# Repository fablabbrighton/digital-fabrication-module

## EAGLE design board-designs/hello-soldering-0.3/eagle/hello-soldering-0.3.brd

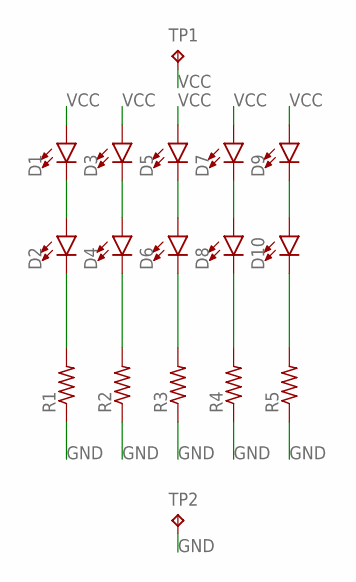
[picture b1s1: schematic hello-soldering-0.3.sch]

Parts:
D1, D2, D3, D4, D5, D6, D7, D8, D9, D10: LED1206; LED-1206
R1, R2, R3, R4, R5: RES-US1206; R1206
TP1, TP2: TPTP20R; TP20R

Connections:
GND: R1.1, R2.1, R3.1, R4.1, R5.1, TP2.TP
unnamed: D1.C, D2.A
unnamed: D2.C, R1.2
unnamed: D3.C, D4.A
unnamed: D4.C, R2.2
unnamed: D5.C, D6.A
unnamed: D6.C, R3.2
unnamed: D8.C, R4.2
unnamed: D10.C, R5.2
unnamed: D7.C, D8.A
unnamed: D9.C, D10.A
VCC: D1.A, D3.A, D5.A, D7.A, D9.A, TP1.TP

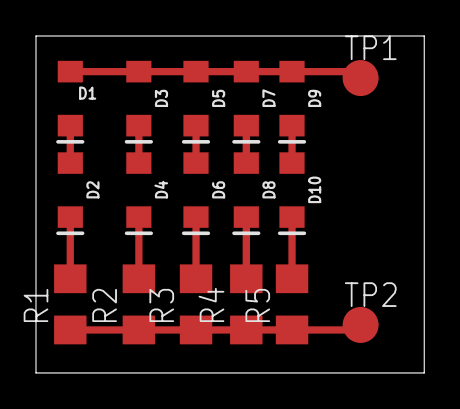
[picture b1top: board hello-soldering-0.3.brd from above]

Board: 2 copper layers, 21.6 x 18.7 mm, 17 parts (0 on the bottom side), 12 nets.

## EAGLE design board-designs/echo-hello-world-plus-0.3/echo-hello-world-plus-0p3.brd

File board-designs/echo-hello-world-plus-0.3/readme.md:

# Readme

This is a minimal ATtiny44-based board, derived from Neil's Echo Hello World board, as used in [Fab Academy Electronics Design week](http://academy.cba.mit.edu/classes/electronics_design/index.html).

It has an additional LED (with current-limiting resistor) and button, to enable simple testing by uploading Arduino blink or button sketches. (Hence the 'Plus' in the name.)

The button needs a pull-up resistor (on the pin, or added externally) to work.

This board is used in our [electronics design week](https://github.com/fablabbrighton/digital-fabrication-module/tree/master/docs/_course-notes/week-5-electronics-design.md).

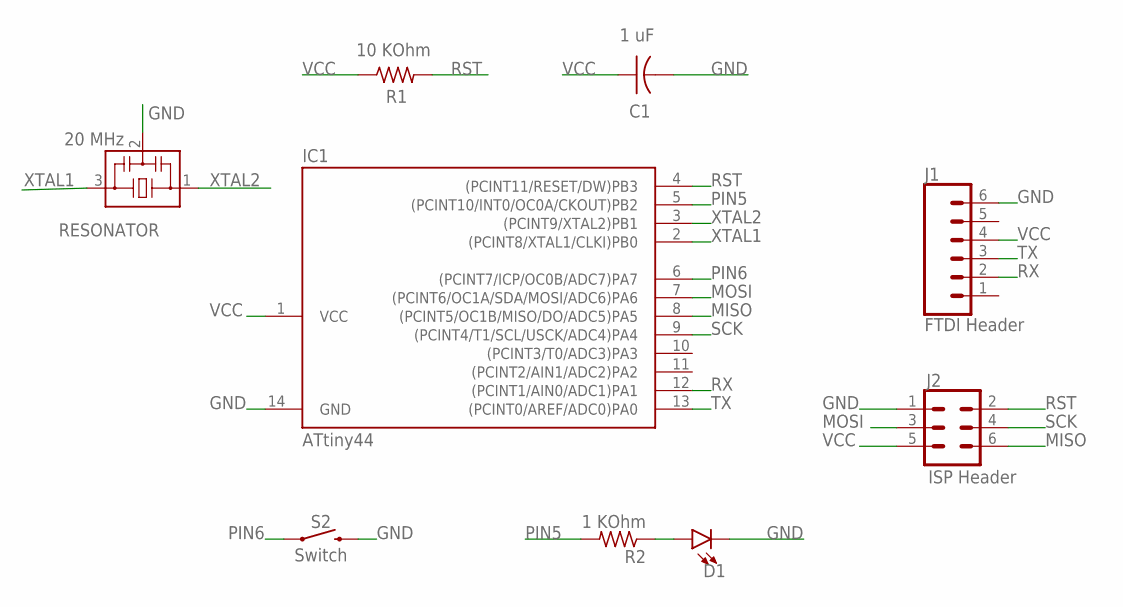
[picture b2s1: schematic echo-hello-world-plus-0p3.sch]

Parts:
C1: 1 uF; C1206
D1: LED1206; LED-1206
IC1: ATtiny44; SOIC14
J1: FTDI Header; 1X06_SMD_MALE
J2: ISP Header; 2X3_SMD
R1: 10 KOhm; R1206
R2: 1 KOhm; M1206
RESONATOR: 20 MHz; EFOBM
S2: Switch; TACTILE_SWITCH_SMD_6.2MM_TALL

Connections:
GND: C1.2, D1.C, IC1.14 (GND), J1.6, J2.1, RESONATOR.2, S2.B2 (2)
MISO: IC1.8 ((PCINT5/OC1B/MISO/DO/ADC5)PA5), J2.6
MOSI: IC1.7 ((PCINT6/OC1A/SDA/MOSI/ADC6)PA6), J2.3
unnamed: D1.A, R2.1
PIN5: IC1.5 ((PCINT10/INT0/OC0A/CKOUT)PB2), R2.2
PIN6: IC1.6 ((PCINT7/ICP/OC0B/ADC7)PA7), S2.A2 (1)
RST: IC1.4 ((PCINT11/RESET/DW)PB3), J2.2, R1.2
RX: IC1.12 ((PCINT1/AIN0/ADC1)PA1), J1.2
SCK: IC1.9 ((PCINT4/T1/SCL/USCK/ADC4)PA4), J2.4
TX: IC1.13 ((PCINT0/AREF/ADC0)PA0), J1.3
VCC: C1.1, IC1.1 (VCC), J1.4, J2.5, R1.1
XTAL1: IC1.2 ((PCINT8/XTAL1/CLKI)PB0), RESONATOR.3
XTAL2: IC1.3 ((PCINT9/XTAL2)PB1), RESONATOR.1

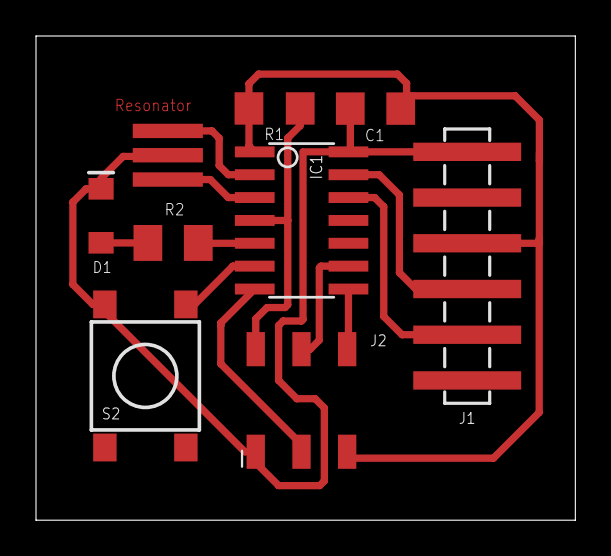
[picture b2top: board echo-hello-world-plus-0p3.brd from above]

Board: 2 copper layers, 30.0 x 26.9 mm, 9 parts (0 on the bottom side), 13 nets.

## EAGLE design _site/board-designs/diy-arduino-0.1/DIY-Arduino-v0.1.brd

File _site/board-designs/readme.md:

Eagle board designs and bitmap exports for milling.

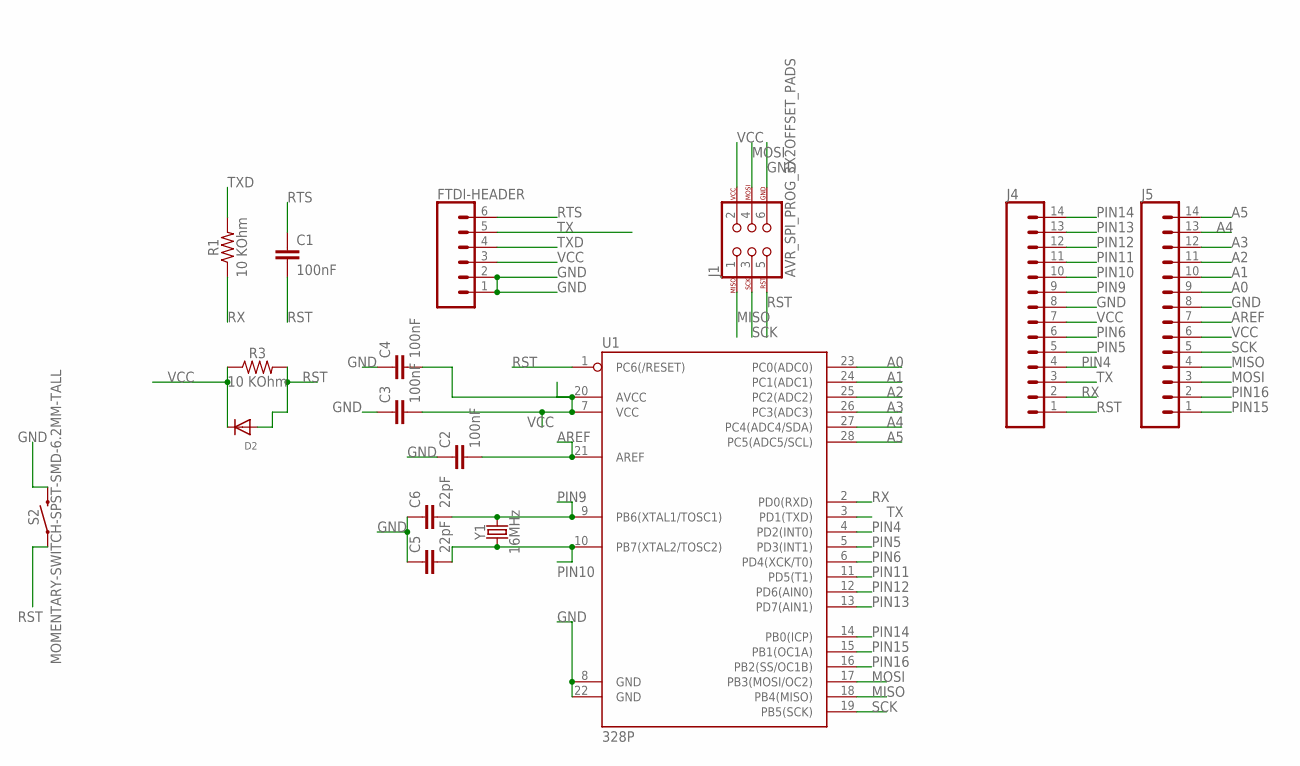
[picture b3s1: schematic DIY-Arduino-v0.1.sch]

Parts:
C1, C2, C3, C4: 100nF; C1206
C5, C6: 22pF; C1206
D2: DIODEDO-1N4148; DO-1N4148
FTDI-HEADER: CONN_06NO_SILK_FEMALE_PTH; 1X06_NO_SILK
J1: AVR_SPI_PROG_3X2OFFSET_PADS; 2X3_OFFSET
J4, J5: CONN_14NO_SILK; 1X14_NO_SILK
R1, R3: 10 KOhm; 1206
S2: MOMENTARY-SWITCH-SPST-SMD-6.2MM-TALL; TACTILE_SWITCH_SMD_6.2MM_TALL
U1: 328P; DIP28
Y1: 16MHz; HC49US

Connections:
A0: J5.9, U1.23 (PC0(ADC0))
A1: J5.10, U1.24 (PC1(ADC1))
A2: J5.11, U1.25 (PC2(ADC2))
A3: J5.12, U1.26 (PC3(ADC3))
A4: J5.13, U1.27 (PC4(ADC4/SDA))
A5: J5.14, U1.28 (PC5(ADC5/SCL))
AREF: C2.2, J5.7, U1.21 (AREF)
GND: C2.1, C3.1, C4.1, C5.1, C6.1, FTDI-HEADER.1, FTDI-HEADER.2, J1.6, J4.8, J5.8, S2.B2 (2), U1.8 (GND), U1.22 (GND)
MISO: J1.1, J5.4, U1.18 (PB4(MISO))
MOSI: J1.4, J5.3, U1.17 (PB3(MOSI/OC2))
PIN4: J4.4, U1.4 (PD2(INT0))
PIN5: J4.5, U1.5 (PD3(INT1))
PIN6: J4.6, U1.6 (PD4(XCK/T0))
PIN9: C6.2, J4.9, U1.9 (PB6(XTAL1/TOSC1)), Y1.2
PIN10: C5.2, J4.10, U1.10 (PB7(XTAL2/TOSC2)), Y1.1
PIN11: J4.11, U1.11 (PD5(T1))
PIN12: J4.12, U1.12 (PD6(AIN0))
PIN13: J4.13, U1.13 (PD7(AIN1))
PIN14: J4.14, U1.14 (PB0(ICP))
PIN15: J5.1, U1.15 (PB1(OC1A))
PIN16: J5.2, U1.16 (PB2(SS/OC1B))
RST: C1.2, D2.A, J1.5, J4.1, R3.2, S2.A2 (1), U1.1 (PC6(/RESET))
RTS: C1.1, FTDI-HEADER.6
RX: J4.2, R1.1, U1.2 (PD0(RXD))
SCK: J1.3, J5.5, U1.19 (PB5(SCK))
TX: FTDI-HEADER.5, J4.3, U1.3 (PD1(TXD))
TXD: FTDI-HEADER.4, R1.2
VCC: C3.2, C4.2, D2.C, FTDI-HEADER.3, J1.2, J4.7, J5.6, R3.1, U1.7 (VCC), U1.20 (AVCC)

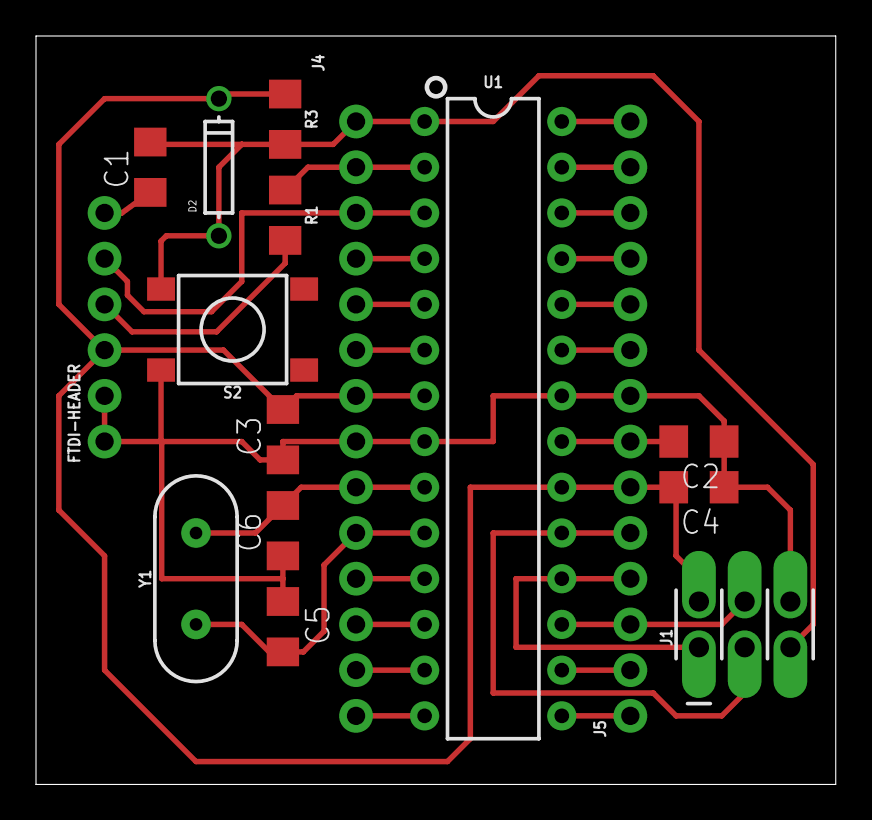
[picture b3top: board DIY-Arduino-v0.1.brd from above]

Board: 2 copper layers, 44.4 x 41.6 mm, 16 parts (0 on the bottom side), 28 nets.

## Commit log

2018-11-17 Set theme jekyll-theme-cayman
2018-11-17 test md page from Bear
2018-11-17 sitemap
2018-11-17 theme for gitbook
2018-11-23 loads of stuff
2018-11-23 Replace html files with md files
2018-11-24 fixing urls on github pages
2018-11-24 config fix
2018-11-24 added readme
2018-11-24 add gitignore file
2018-11-24 removed gitignore file
2018-11-24 Remove the now ignored directory "_site-ascom"
2018-11-24 Remove the now ignored directory "_site"
2018-11-24 Remove some other superfluous files
2018-11-24 removed gemfiles from gitignore
2018-11-25 fiddling with docs folder
2018-11-25 moved content to docs folder
2018-11-25 Remove _site folders after moving to docs
2018-11-25 add readmes to empty folders
2018-11-25 file structure notes
2018-11-25 move gemfile
2018-11-25 new collections content and structure
2018-11-25 fixed {{ site.baseurl }} in notes
2018-11-26 styling changes mostly
2018-12-05 diy arduino notes and schematics
2018-12-05 Eagle design
2018-12-07 elctronics production course notes
2018-12-07 exclude colophone from homepage
2018-12-15 mostly edits to electronics design and eagle guide
2018-12-15 fixed image urls
2018-12-16 programming guide
2018-12-19 programming programmer guide
2018-12-20 echo hello world plus board
2018-12-20 programming a board
2018-12-21 testing image link URLs
2018-12-21 Fix image links
2019-01-02 minimal-parametric-laser-cutter-demo
2019-01-02 weeks 3 and 6
2019-01-02 fix guide urls
2019-01-07 mostly electronics production updates
2019-01-31 add week 1 content. add author support to templates
2019-01-31 Initial push kjk
2019-01-31 Update readme.md
    Making some changes to support transfer to fablabbrighton
2019-01-31 some changes to reflect transfer
2019-01-31 add author to my posts
2019-01-31 more url fixes
2019-02-06 minor text fixes
2019-02-06 fix sorting on homepage and course notes index
2019-02-06 header hr
2019-02-11 minor fixes
2019-02-11 title fix
2019-02-11 Rename week-2-computer-aided-design-solidworks.md to week-2-alternative-computer-aided-design-solidworks.md
2019-02-11 Update week-1-intro-websites-project-management.md
    added youtube embed video link
2019-02-22 add files for soldering board
2019-02-22 soldering amends
2019-02-25 fabisp parts
2019-02-25 board milling guide
2019-02-25 soldering board guide
2019-02-25 hello-soldering board designs
2019-03-05 Create week-7-3d-printing-scanning
2019-03-05 Create week-8-moulding-casting
2019-03-05 Update week-7-3d-printing-scanning
2019-03-12 Update guide-milling-board.md
    home fix
2019-03-12 Update week-6-embedded-programming.md
    Add https://www.tinkercad.com option
2019-03-12 Rename week-7-3d-printing-scanning to week-7-3d-printing-scanning.md
2019-03-12 Update and rename week-8-moulding-casting to week-8-machining+moulding-casting
2019-03-12 Update week-8-machining+moulding-casting
2019-03-12 Rename week-8-machining+moulding-casting to week-8-machining+moulding-casting.md
2019-03-16 Create guide-milling-mould-tool
2019-03-19 Add Hello328p as submodule under board designs
2019-03-19 Add Hello328p docs
2020-01-02 Initial files for LM225
2020-01-02 project dev
2020-01-02 assessment
2020-01-02 IA changes
2020-01-02 move lm225 files to course-notes-lm225-2020
2020-01-02 formative
2020-01-02 page formatting
2020-01-02 add jekyll page metadata
2020-01-03 split 3D machines
2020-01-03 change index to readme
2020-01-09 small updates
2020-01-14 assessement changes
2020-01-14 intro and prep
2020-01-17 hand
2020-01-17 example test
2020-01-17 memento rug
2020-01-17 archisuits
2020-01-17 self-forming-structures
2020-01-17 examples
2020-01-17 3d-print-concrete
2020-01-29 mostly handbook fixes
2020-01-29 assesment fixes
2020-02-05 laser notes
2020-02-12 pinout
2020-02-12 breadboards
2020-02-20 cura
2020-02-25 microbit
2020-02-28 fusion
2020-02-28 more fusion demos
2020-02-28 fusion 3
2020-03-02 3D and microbit changes
2020-03-09 milling docs
2020-03-30 coronavirus projects
2020-04-03 date changes
2021-07-13 Bump addressable from 2.5.2 to 2.8.0
    Bumps [addressable](https://github.com/sporkmonger/addressable) from 2.5.2 to 2.8.0.
    - [Release notes](https://github.com/sporkmonger/addressable/releases)
    - [Changelog](https://github.com/sporkmonger/addressable/blob/main/CHANGELOG.md)
    - [Commits](https://github.com/sporkmonger/addressable/compare/addressable-2.5.2...addressable-2.8.0)
    ---
    updated-dependencies:
2022-10-06 Bump addressable from 2.5.2 to 2.8.1
    Bumps [addressable](https://github.com/sporkmonger/addressable) from 2.5.2 to 2.8.1.
    - [Release notes](https://github.com/sporkmonger/addressable/releases)
    - [Changelog](https://github.com/sporkmonger/addressable/blob/main/CHANGELOG.md)
    - [Commits](https://github.com/sporkmonger/addressable/compare/addressable-2.5.2...addressable-2.8.1)
    ---
    updated-dependencies:

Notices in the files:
parts and their libraries:
SparkFun-IC-Microcontroller: Licensing: Creative Commons ShareAlike 4.0 International - https://creativecommons.org/licenses/by-sa/4.0
